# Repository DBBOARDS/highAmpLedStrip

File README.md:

# highAmpLedStrip
Connect to and Control 5V LED Strips Easily and Safely with the High Amperage LED Strip Board

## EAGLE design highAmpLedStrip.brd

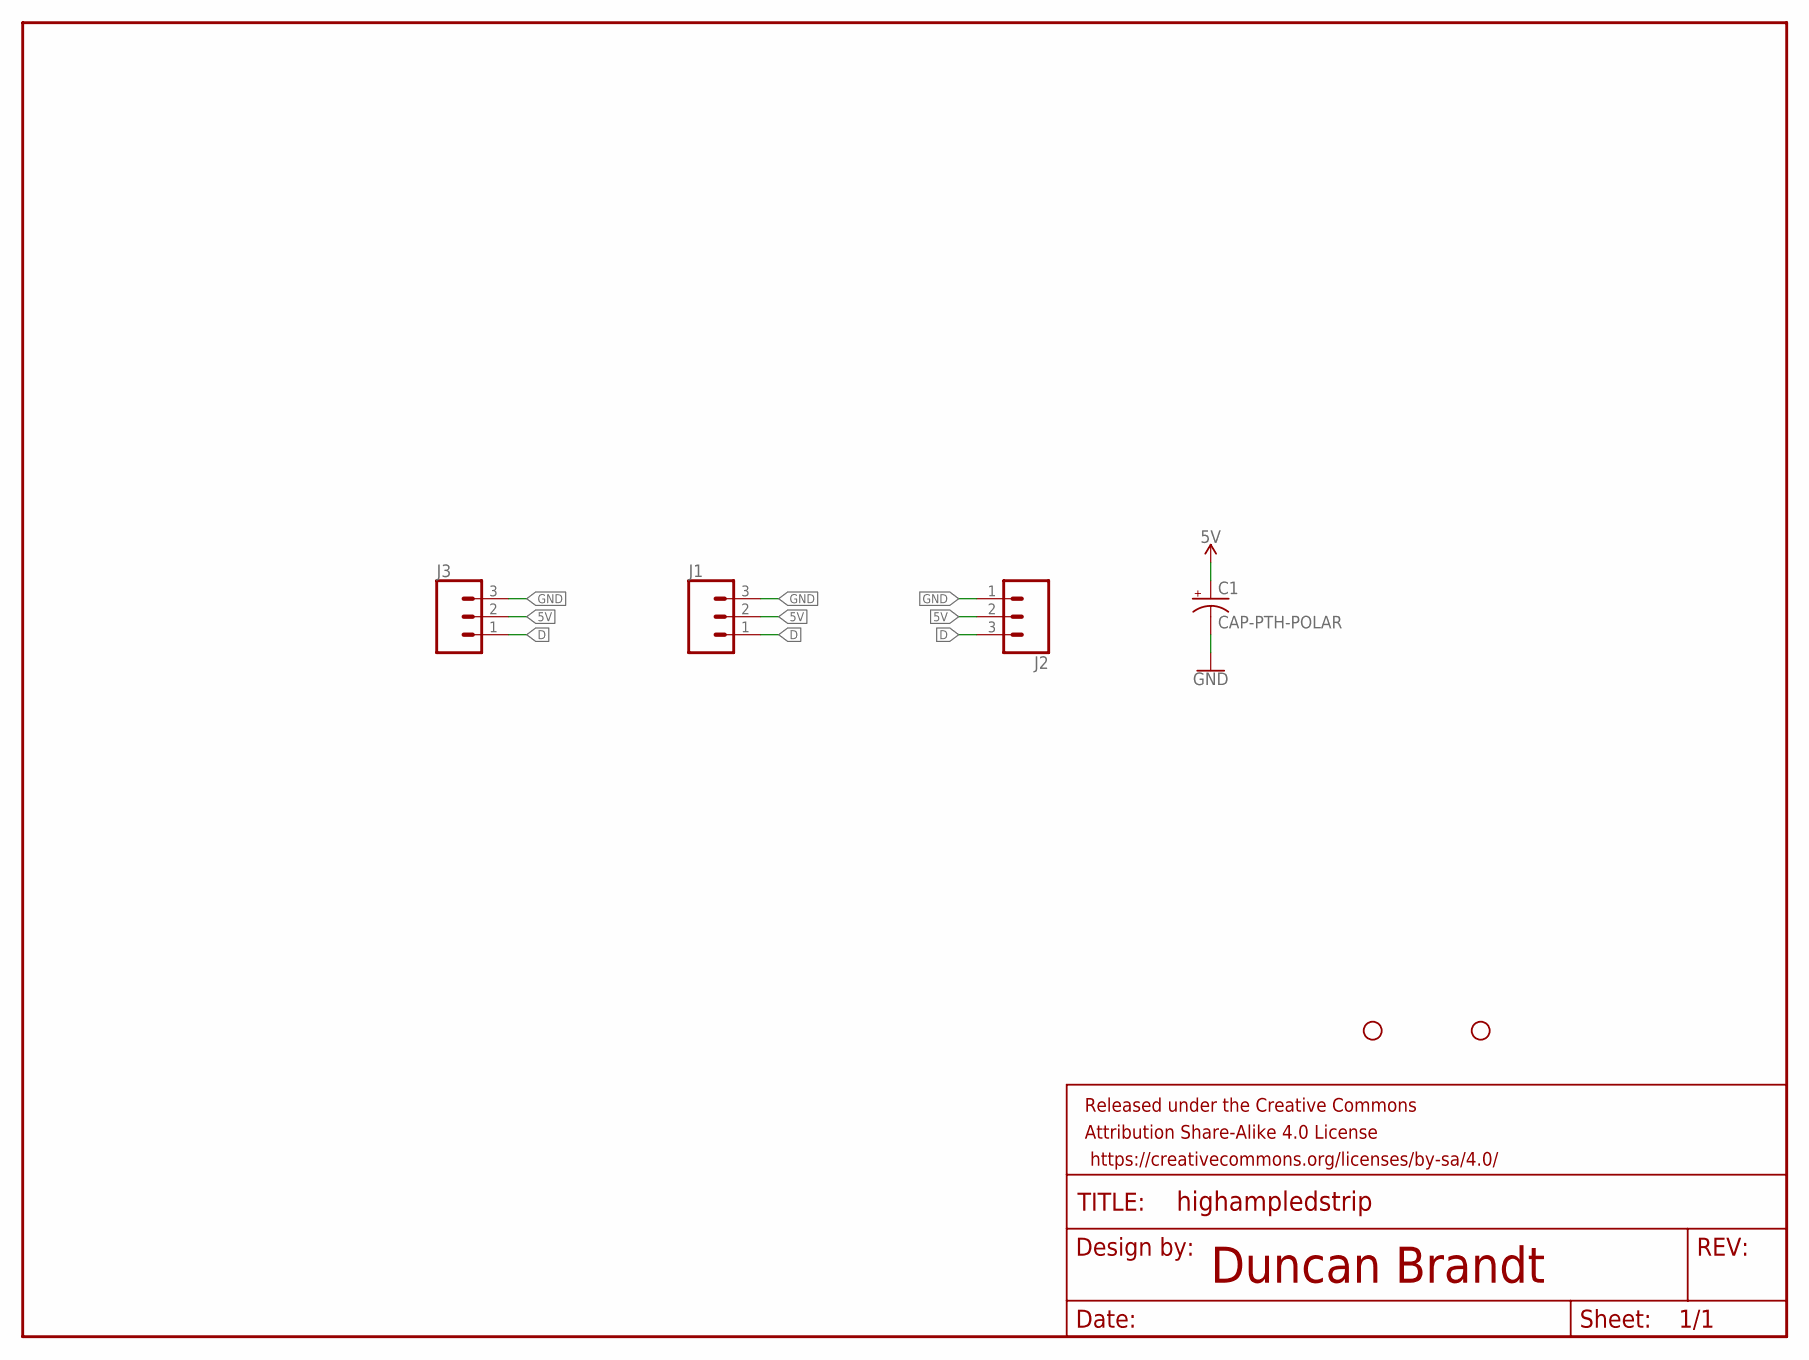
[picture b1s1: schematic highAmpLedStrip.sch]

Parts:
C1: CAP-PTH-POLAR; CPOL-RADIAL-2.5MM-5MM
FRAME1: FRAME-LETTER; CREATIVE_COMMONS
H1, H2: STAND-OFF
J1: CONN_03LONGPADS; 1X03_LEDSTRIP_LONGPADS
J2: CONN_031X03_NO_SILK; 1X03_5MM_SCREWTERM
J3: CONN_03; 1X03

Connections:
5V: C1.1 (+), J1.2, J2.2, J3.2
D: J1.1, J2.3, J3.1
GND: C1.2 (-), J1.3, J2.1, J3.3

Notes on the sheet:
Duncan Brandt

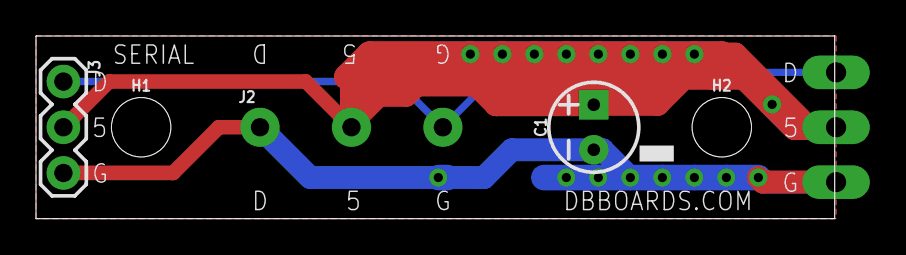
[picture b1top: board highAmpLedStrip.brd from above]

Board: 2 copper layers, 44.4 x 10.2 mm, 7 parts (1 on the bottom side), 3 nets.

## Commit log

2018-01-31 Eagle Files for High Amperage LED Strip Board

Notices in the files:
parts and their libraries:
DB-SYMBOLS: Licensing: Creative Commons ShareAlike 4.0 International - https://creativecommons.org/licenses/by-sa/4.0
DB-SYMBOLS: Released under the Creative Commons Attribution Share-Alike 4.0 License
DB-SYMBOLS: https://creativecommons.org/licenses/by-sa/4.0
